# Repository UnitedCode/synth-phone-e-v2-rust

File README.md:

# Synthphone E

Rust firmware for a **Daisy Seed synth and vocal effects processor**
(STM32H750 Cortex-M7).

- **Voice:** pitch correction, formant effects, vocoder and MIDI-controlled harmony.
- **Instruments:** polyphonic MIDI synth and digitally synthesized drums.
- **Controls:** phone keypad, rotary encoder and 128×32 OLED.

## Build

Install [Rust](https://www.rust-lang.org/tools/install), then run these commands
from the repository root:

```sh
rustup target add thumbv7em-none-eabihf
cargo build --release --locked
```

**Output:** `target/thumbv7em-none-eabihf/release/app`. Building does not flash the device.

## Flash to a Daisy Seed

Install [probe-rs](https://probe.rs/docs/getting-started/installation/) and connect
the Seed through an **SWD debug probe**, then run:

```sh
cargo run --release --locked
```

The chip and runner are configured in [.cargo/config.toml](.cargo/config.toml).
For RTT logging and a GDB server on `localhost:1337`, use `cargo embed --release`
with [Embed.toml](Embed.toml).

## Modes

| On-screen name | What it does |
| --- | --- |
| Pitch Ctrl | Pitch correction and vocal pitch/formant effects |
| Vocode | Vocoder with note-controlled carrier |
| Synth+Vox | Synth with uncorrected vocals |
| Synth+Tune | Synth with pitch-corrected vocals |
| Harmony | MIDI-controlled vocal harmonies |
| Percussion | Synthesized drums |

For Harmony, start with chords on **MIDI channel 1**. See the
[MIDI harmony guide](docs/harmony-midi.md) for lead/backing channels and controls.

In Vocode, adjust **Vocode Amount** in the encoder menu: **0** is your natural
voice, **5** is a 50/50 blend (default), and **10** is the full effect.
Double-press the encoder to open the menu. The setting saves automatically;
MIDI **CC49** also controls it (0–127 maps to 0–10).

For Harmony, Pitch Ctrl and Synth+Tune, **Voice Range** selects the tracker’s
lowest source pitch: **All** = 50 Hz (default), **Mid** = 100 Hz, **Hi** = 150 Hz.
Try **Hi** for the tested vocal; use **All** for low voices. It saves automatically.
MIDI **CC50** values **0 / 64 / 127** select All / Mid / Hi.

## Check changes without hardware

These commands use a POSIX shell (macOS/Linux). The explicit host target is
required because this repo defaults to ARM.

```sh
LAB_HOST=$(rustc -vV | sed -n 's/^host: //p')
cargo fmt --all -- --check
cargo test --locked --lib --target "$LAB_HOST"
cargo test --release --locked --manifest-path tools/audio-lab/Cargo.toml --target "$LAB_HOST"
```

The audio lab checks vocal DSP and MIDI behavior. For WAV replay, pitch sweeps
and measurements, see [audio testing](docs/audio-testing.md).

To boot the production firmware in an emulator, follow the
[Virtual Daisy guide](docs/virtual-daisy.md). Initialize its pinned submodule first:

```sh
git submodule update --init tools/virtual-daisy
```

**Hardware validation is still needed** for real-time deadlines, analog audio
and musical feel. See the [conformance gaps](docs/daisy-conformance.md).

## Find your way around

| Location | Purpose |
| --- | --- |
| [src/main.rs](src/main.rs) | RTIC tasks, hardware setup and audio routing |
| [src/state_machine/](src/state_machine/) | Modes, menus and settings |
| [src/audio/](src/audio/) · [src/midi/](src/midi/) | Audio processing, synth voices and MIDI |
| [src/input/](src/input/) · [src/display/](src/display/) | Buttons, encoder and OLED |
| [tools/audio-lab/](tools/audio-lab/) | Host DSP tests and WAV tools |
| [tools/virtual-daisy/](tools/virtual-daisy/) | Pinned firmware emulator |

FFT vocal effects come from the pinned
[`synthphone-e-vocal-dsp` dependency](https://github.com/nathansbradshaw/synthphone_e_vocal_dsp).
For deeper checks, see [ARM DSP emulation](docs/arm-emulation.md) and the
[pitch audit](docs/pitch-audit.md).

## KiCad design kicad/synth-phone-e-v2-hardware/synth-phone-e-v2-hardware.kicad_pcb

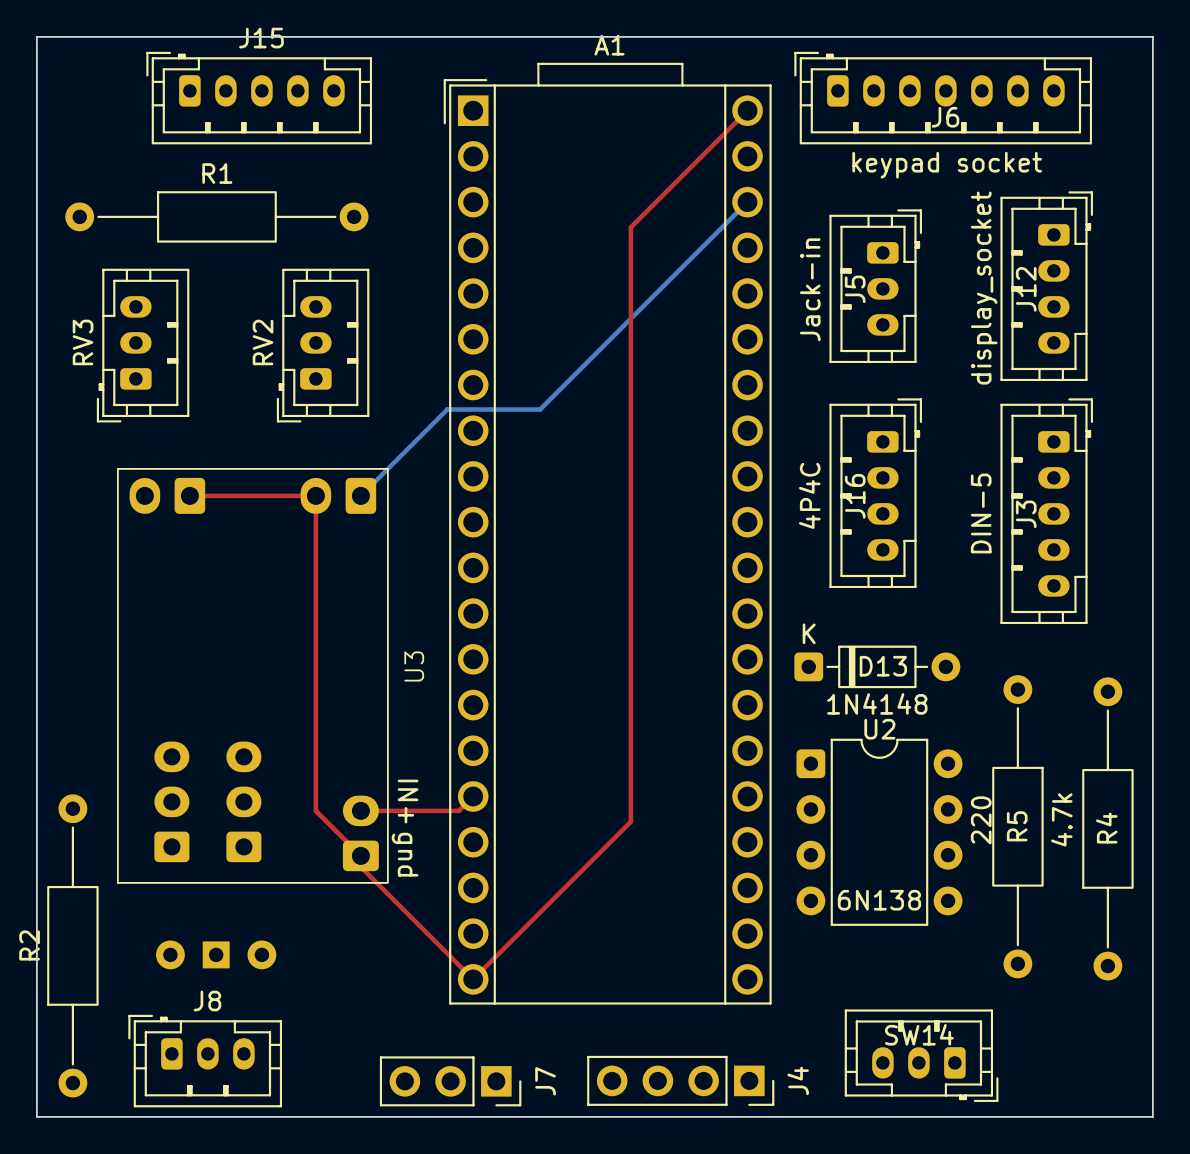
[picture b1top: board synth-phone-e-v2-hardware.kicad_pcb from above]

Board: 2 copper layers, 62.0 x 60.0 mm, 21 parts (1 on the bottom side), 33 nets.

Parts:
A1: Electrosmith_Daisy_Seed_Rev4; Electrosmith_Daisy_Seed
D13: 1N4148; D_DO-35_SOD27_P7.62mm_Horizontal
J3: DIN-5; JST_PH_B5B-PH-K_1x05_P2.00mm_Vertical
J4: Keypad_column_output; PinSocket_1x04_P2.54mm_Vertical
J5: Jack-in; JST_PH_B3B-PH-K_1x03_P2.00mm_Vertical
J6: keypad socket; JST_PH_B7B-PH-K_1x07_P2.00mm_Vertical
J7: keypad_row_output; PinSocket_1x03_P2.54mm_Vertical
J8: jack-out; JST_PH_B3B-PH-K_1x03_P2.00mm_Vertical
J12: display_socket; JST_PH_B4B-PH-K_1x04_P2.00mm_Vertical
J15: encoder_input; JST_PH_B5B-PH-K_1x05_P2.00mm_Vertical
J16: 4P4C; JST_PH_B4B-PH-K_1x04_P2.00mm_Vertical
R1, R5: 220; R_Axial_DIN0207_L6.3mm_D2.5mm_P15.24mm_Horizontal
R2: ?; R_Axial_DIN0207_L6.3mm_D2.5mm_P15.24mm_Horizontal
R4: 4.7k; R_Axial_DIN0207_L6.3mm_D2.5mm_P15.24mm_Horizontal
RV2, RV3: R_Potentiometer_Trim_US; JST_PH_B3B-PH-K_1x03_P2.00mm_Vertical
SW13: SW_Wuerth_450301014042; SW_Slide-03_Wuerth-WS-SLTV_10x2.5x6.4_P2.54mm
SW14: SW_Push_SPDT; JST_PH_B3B-PH-K_1x03_P2.00mm_Vertical
U2: 6N138; DIP-8_W7.62mm
U3: ssm2167

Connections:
AUDIO_IN_1_4p4c: R2.2, SW13.1 (B), U3.3 (IN+)
AUDIO_IN_1_jack: A1.17 (AUDIO_IN_2), J5.1, J5.2
AUDIO_IN_AMP: A1.16 (AUDIO_IN_1), U3.5 (OUT+)
AUDIO_OUT_1: A1.18 (AUDIO_OUT_1), J8.2
AUDIO_OUT_2: A1.19 (AUDIO_OUT_2), J8.1
MIDI_in_device: A1.15 (USART1_RX), R5.1, U2.6 (VO2)
unnamed: D13.2 (A), R1.2, U2.2 (C1)
unnamed: D13.1 (K), J3.4, U2.3 (C2)
unnamed: J3.2, R1.1
unnamed: RV3.3, U3.7 (R2L)
unnamed: RV3.2, U3.8 (R2M)
unnamed: RV3.1, U3.9 (R2R)
unnamed: RV2.3, U3.10 (R1L)
unnamed: RV2.2, U3.11 (R1M)
unnamed: RV2.1, U3.12 (R1R)
unnamed: J16.3, SW13.3 (A)
unnamed: J16.4, SW13.2 (C)
unnamed: R4.2, U2.7 (VO1)
SCL: A1.12 (I2C1_SCL), J12.2
SDA: A1.13 (I2C1_SDA), J12.1
channel_selector: A1.2 (SD_DATA_3), SW14.2 (B)
clk: A1.5 (SD_DATA_0), J15.5
col1: A1.26 (ADC_4), J6.3, J7.1
col2: A1.27 (ADC_5), J6.2, J7.2
col3: A1.28 (ADC_6), J6.1, J7.3
dt: A1.4 (SD_DATA_1), J15.4
gnd: A1.20 (AGND), A1.40 (DGND), J3.3, J5.3, J8.3, J12.4, J15.1, J16.1, J16.2, R2.1, R4.1, SW14.3 (C), U2.5 (GND), U3.2 (gnd), U3.4 (IN-), U3.6 (OUT-)
row1: A1.22 (ADC_0), J4.1, J6.7
row2: A1.23 (ADC_1), J4.2, J6.6
row3: A1.24 (ADC_2), J4.3, J6.5
row4: A1.25 (ADC_3), J4.4, J6.4
sw: A1.3 (SD_DATA_2), J15.3
vcc: A1.38 (3V3_D), J12.3, J15.2, R5.2, SW14.1 (A), U2.8 (VCC), U3.1 (vcc)

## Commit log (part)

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2024-06-20 add QEMU runner
2024-06-20 debug: madness
    There is something wrong with the circular buff, this is evident in the fact that the increasing the ring buffer increases the amount of time that the audio is correct.
2024-07-15 chore: update libdaisy
2024-07-19 feat: switch to smaller block size
2024-07-24 feat: fix underrun
2024-07-24 Feat/better vocoder (#8)
    * wip: vocoder not optimized
    wi
    * feat: software task
    * feat: add pot
    * wip: optimizations
    * attempt to speed up locks
2024-07-25 feat: basic ci
2024-08-03 start autotune code
2024-08-03 start auto tune
2024-08-03 Revert "start autotune code"
    This reverts commit c7b79044e594247af025268822c7d0c8c6b3bc78.
2024-08-05 feat: speed up frequency detection
2024-08-05 feat: persist synth
2024-08-08 feat: basic setup for tests
2024-08-10 add a noise floor
2024-08-11 start Selective emphasis
2024-08-19 wip: split lib to core lib
2024-08-22 feat:
2024-08-31 fix errors
2024-09-06 init
2024-09-07 move lib files out
2024-09-07 chore: update readme
2024-09-07 chore: cargo fmt
2024-09-07 chore: update build ci/cd
2024-09-08 feat: Ferrous system setup (#10)
    * init
    * move lib files out
    * chore: update readme
    * chore: cargo fmt
    * chore: update build ci/cd
    * chore: cargo fmt
2024-09-19 feat: some supper buggy auto tune
2024-09-19 chore: stub test
2024-09-21 feat: host version of app
2024-09-21 wip: comment out everygthing
2024-09-22 feat: validate pitch detection
2024-09-22 feat: autotune!
2024-09-23 feat: update embedded device to use new autotuner
2024-09-23 feat: key of c
2024-09-23 Feat/basic auto tune (#9)
    * start autotune code
    * start auto tune
    * Revert "start autotune code"
    This reverts commit c7b79044e594247af025268822c7d0c8c6b3bc78.
    * feat: speed up frequency detection
    * feat: persist synth
2024-09-26 chore: setup kicad
2024-10-03 feat: encoder state machine
2024-10-04 feat: github action for generating schematic
2024-10-17 chore: remove unused libraries
2024-11-07 feat: basic lcd
2024-11-16 feat: display?
2024-11-16 fix: error?
2024-11-16 wip screen w/ new logo
2024-12-05 feat: basic encoder functionality
2024-12-07 feat: add buttons
2024-12-07 Feat/add encoder (#11)
    * chore: setup kicad
    * feat: encoder state machine
    * feat: github action for generating schematic
    * chore: cargo fmt
    * chore: remove unused libraries
    * feat: basic lcd
2024-12-12 chore: code cleanup
2024-12-19 wip: begin adding state machine to main code block
2025-01-04 state machine madness
2025-01-04 WIP draw values to screen
2025-01-09 feat: integrate screen with state machine
2025-01-10 feat: basic sub menu
2025-01-10 fix sub menu spacing
2025-01-23 add scales
2025-01-23 feat: add frequencies lut
2025-03-01 add crush
2025-03-01 bit crush with sample reduction
2025-04-27 i don't even remember
2025-05-18 chore: update schematic
2025-05-19 WIP gut state machine
2025-05-19 WIP new state machine
2025-05-20 state machine in semi working state
2025-05-20 fix broken notes
2025-05-20 fix double click
2025-05-20 add performance effects profile screen
2025-05-20 fix name
2025-05-21 fix mode issue an naming
2025-05-22 chore: wip circuit board
2025-05-22 mostly working process and effects screens
2025-05-22 try to add volume
2025-05-22 visual feedback of keypresses
2025-05-22 attempted menu fix
2025-05-22 test and fix button effects
2025-05-23 feat: finish pcb
2025-05-25 fix the flipped
2025-05-26 fix note off issues
2025-05-26 fix underline
2025-05-29 fix code
2025-05-29 fix: test?
2025-05-29 chore: move files around. (#40)
    * move files
    * chore: cargo fmt
    * fix: test?
    * Update test.yml
    * Update test.yml
    * Update frequencies.rs
2025-05-29 chore: move stuff around
2025-06-01 hook up UI
2025-06-01 change the state machine to the correct values
2025-06-01 add a saw wave
2025-06-02 semi working vocoder
2025-06-02 latch when vocoding
2025-06-02 get frequency
2025-06-02 formatting
2025-06-02 just play saw
2025-06-03 move into seperate processes for now
2025-06-04 all 3 process states in semi working states
2025-06-05 chore: move stuff around (#41)
2025-06-11 working autotune and vocode! no noise!
2025-06-11 working vocoder!
2025-06-11 add effects back in
2025-06-12 add in formant shifting
2025-06-12 working formant shifter in autotune
2025-06-12 pitch shifting for dry which i will rename to vox because it is now a wet ass process
2025-06-13 manual tune
2025-06-13 dry synth
2025-06-13 oosp
2025-06-14 attempt to speed up
2025-06-18 add ring buffer
2025-06-18 move display to low priority task
2025-06-21 try to make fast
2025-06-21 fixes
2025-06-26 Vocoder actual (#55)
    * chore: move stuff around
    * change the state machine to the correct values
    * hook up ui
    * add a saw wave
    * semi working vocoder
    * latch when vocoding
2025-06-26 Revert "Merge remote-tracking branch 'origin/main' into make-fast"
    This reverts commit 39c1b9ce816ede0e4d4496fdd6ee4ca2ddcde423, reversing
    changes made to 24884c7f1642b74bf480e285d7f2936c8edf32de.
2025-06-28 chore: add rust analyse
2025-06-28 chore: add rust-analyzer lock files
2025-06-28 chore: fix formatting
2025-06-28 chore: update handler
2025-06-28 feat: add volume
2025-07-01 experimental change on timing
2025-07-10 wip: midi
2025-07-26 wip harmonizer
2025-08-10 make encoder cut to next screen too
2025-09-15 wip: wire up new voice library
2025-09-16 chore: remove local autotune library
2025-09-16 feat: simplify code base
2025-09-19 feat: use new api
2025-09-19 wip formant settings
2025-09-20 did not fix but makes really cool noice when you switch through all the modes
2025-09-20 fix: no audio
2025-09-20 chore: use new name of libarary
2025-09-20 chore: use the github library for the vocal effects
2025-09-20 fix: vocode and dryvox
2025-09-20 fix: buttons holding till screen updates
2025-09-20 add back octave and make the encoder spin the right way
2025-09-21 wip: comment out midi for now
2025-09-24 feat: basic midi support
2025-09-24 feat: basic midi output
2025-09-25 feat: move midi to interrupt task
2025-09-25 add back octave and make the encoder spin the right way (#64)
2025-09-25 chore: move things around
2025-09-25 add full spritesheet
2025-09-25 try to vocode
2025-09-25 fix room for text
2025-09-26 add volume to perform prof
2025-09-26 add wave form option and handle when to show
2025-09-26 idk what your robot wants from me
2025-09-27 UI optimization (#67)
    * add full spritesheet
    * fix room for text
    * add volume to perform prof
    * add wave form option and handle when to show
    * idk what your robot wants from me
    * to appease the robot grammar nazi
2025-09-27 single location for sprites and do not build them each time
2025-09-29 feat: hook up oscillator style change
2025-09-29 wip split out text styles
2025-09-30 move styles to text file
2025-09-30 everything must go
2025-09-30 instantiate the atlas once
2025-09-30 clears are not needed since we draw over everything
2025-09-30 appease the robot
2025-09-30 UI optimization (#70)
    * add full spritesheet
    * fix room for text
    * add volume to perform prof
    * add wave form option and handle when to show
    * idk what your robot wants from me
    * to appease the robot grammar nazi
2025-10-01 wip harmony
2025-10-01 Feat midi support (#63)
    * wip: midi support
    * wip: comment out midi for now
    * feat: basic midi support
    * feat: basic midi output
    * feat: move midi to interrupt task
    * chore: move things around
2025-10-01 encoder press exits splash
2025-10-03 feat: transition splash to normal on load
2025-10-03 appease the enochs
2025-10-03 feat: transition splash to normal on load (#75)
    * feat: transition splash to normal on load
    * appease the enochs
2025-10-10 chore: use i8 where can
2025-10-10 chore: use a macro
    gonnaa sneak this in
2025-10-10 chore: use i8 where can (#78)
    * chore: use i8 where can
    * chore: use a macro
    gonnaa sneak this in
2025-10-10 rename dirty word
2025-10-10 missed one
2025-10-14 phone is dry but with 2 tone on the synth side
2025-10-15 if it please the robot
2025-10-31 attempt to fox my no nos
2025-11-20 WIP drum
2025-11-27 wip - handle multiple voice types
2025-11-27 forgot
2025-12-02 wip - working drums
2025-12-17 drum working
2026-01-07 wip add percussion profile ui
2026-01-08 wip percussion
2026-01-10 refactor: optimize UI rendering with caching and dirty tracking
2026-01-10 fix: build errors
2026-03-18 change name to percussion
2026-06-12 fix: notes stay the same volume regardless of number of notes
2026-06-13 chore: linting
2026-06-13 Feat percussion profile (#103)
    * wip add percussion profile ui
    * wip percussion
    * change name to percussion
    * fix: notes stay the same volume regardless of number of notes
    * chore: linting
    ---------
2026-06-14 chore: Refactor audio/MIDI handling
    Update embedded audio/MIDI code for performance and clarity, add repository guidance, and tweak ignores.
    Changes:
    - Add CLAUDE.md with project overview, build/flash instructions, architecture and development notes.
    - .gitignore: add .DS_Store and normalize newline.
    - Cargo.toml: bump synthphone-e-vocal-dsp to a newer commit (resource reduction).
    - src/handler.rs: remove shared locking for sample-rate-reduction by passing sr_hold_counter and sr_held_value as local params into audio_handler; simplify app-state snapshot handling in vocal effect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
2026-06-14 chore: Refactor audio/MIDI handling (#104)
    * chore: Refactor audio/MIDI handling
    Update embedded audio/MIDI code for performance and clarity, add repository guidance, and tweak ignores.
    Changes:
    - Add CLAUDE.md with project overview, build/flash instructions, architecture and development notes.
    - .gitignore: add .DS_Store and normalize newline.
    - Cargo.toml: bump synthphone-e-vocal-dsp to a newer commit (resource reduction).
2026-06-15 feat: basic vocoder midi
2026-06-15 feat: multi note vocode midi
2026-06-15 Feat basic vocoder midi (#105)
    * feat: basic vocoder midi
    * feat: multi note vocode midi
    * Update Cargo.lock
2026-06-15 feat: split voice and sound by channels
2026-06-15 feat: split voice and sound by channels (#106)
2026-06-16 feat: drum profile
2026-06-16 handle more midi events and formant correct harmonies
2026-06-17 feat: drums polyphonic
2026-06-17 make polyphonic
2026-06-18 Move percussion MIDI to handler; remove queue
    Remove the queued drum-note mechanism from the state machine and inject percussion MIDI events directly from the UI/input layer. handler.rs no longer drains pending drum notes; interface press handli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
2026-06-18 feat: drum profile (#107)
    * feat: drum profile
    * Update drum_synth.rs
    * feat: drums polyphonic
    * make polyphonic
    * Move percussion MIDI to handler; remove queue
    Remove the queued drum-note mechanism from the state machine and inject percussion MIDI events directly from the UI/input layer. handler.rs no longer drains pending drum notes; interface press handli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
2026-06-19 fix keypad notes
2026-06-21 update cargo lock
2026-06-21 add back in mix
2026-06-21 handle more midi events and formant correct harmonies (#108)
    * handle more midi events and formant correct harmonies
    * Update Cargo.toml
    * update cargo lock
    * add back in mix
    ---------
2026-06-24 Add octave presets, menu refactor & tests
    Introduce octave presets and refactor menu/state handling: add separate octave_low/octave_high menu values and a current_octave_preset (0=low,1=normal,2=high). Snapshot now derives the actual octave 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
2026-06-24 Show active MIDI note and expose lib target
    Add support for displaying the currently active MIDI note and expose the state machine as a library for host tests. Changes include:
    - Add a [lib] entry to Cargo.toml and new src/lib.rs to expose state_machine for host unit tests.
    - Update CLAUDE.md to document running host tests with an explicit target and where tests live.
    - Propagate midi_note_number through the display update snapshot (main.rs) and use it in draw_processing_screen to show chromatic names (use NOTE_NAMES) when a MIDI note is active; fall back to keypa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
    - Update audio handler to track non-drum NoteOn/NoteOff events, call AppStateMachine::set_midi_note / c
